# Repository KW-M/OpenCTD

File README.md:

# OpenCTD SSROV / Education Edition!

This fork contains a modified version of the [OpenCTD](https://github.com/OceanographyforEveryone/OpenCTD) designed to be more reliable, easy to use, and useful as a hands-on classroom teaching tool - Developed for the [SSROV Summer Camp](https://ssrovcamp.org/) - Funding provided by the camp and the National Science Foundation

**Improvements**

- Much more reliable magnetic switch - hold to power on/off - works while fully sealed!
- Data download, calibration & configuration over USB - removes the need to take anything out of the tube or change firmware for use & calibration.
- Supports realtime plotting of sensors via the Arduino serial plotter.
- Configurable sample rate for fast response or extended battery life.
- Bright status LEDs that work in sunlight
- Includes proto space for extending with your own sensors or components.
- Built in slots for ambient lux and 9-axis orientation sensors.
- Connectors make major conmponents, mainboard and tube easily replaceable.
- Factory assembly PCB design - less soldering required and better components for very resonable prices via JLCPCB (30$ + shipping for 5 assembled boards).

**There are many other great open source CTDs used for different applications**

CTDizzle: https://github.com/IanTBlack/CTDizzle

Arduino-based Sonde: https://github.com/glockridge/DrifterApplication

OpenCTD: https://github.com/OceanographyforEveryone/OpenCTD

PiCTD: https://github.com/haanhouse/pictd

## Make your own

> Build and ordering guides comming soon

All things related to the SSROV OpenCTD are found in the [SSROV CTD](./SSROV%20CTD/) folder including:

- [Source code](./SSROV%20CTD/Software/Firmware/ssrov_ctd_code) in Arduino c++ and [pre-compiled binaries](./SSROV%20CTD/Software/Firmware/ssrov_ctd_code/build) for the Adafruit Feather Adalogger - M0 microcontroller.
- [PCB designs](./SSROV%20CTD/Hardware/Electronics/PCB/ssrov-kicad-openctd) in KiCad and exported [pcb trace & assembly files](./SSROV%20CTD/Hardware/Electronics/PCB/ssrov-kicad-openctd/production/) for ordering assembled circuit boards from JLCPCB.
- [3D Printer files](./SSROV%20CTD/Hardware/3D-Prints) and [CAD Designs](https://cad.onshape.com/documents/1210ba157fe929ee8ac86200/w/c68b7dc340291ef5042e473d/e/f126e805a19383355f9e1651) for Onshape.

Submit a github issue and let us know if you want make one or modify for your usecase! - We are happy to help!

### Development Notes:

> Please be advised that the rubber o-rings in the yellow Cherne brand endcaps is much stiffer than the rubber used in other endcap brands and has been found to fail consistently in cold water. We do not recommend using Cherne endcaps in your CTD build.
>
> Some batteries ordered from Amazon have the positive and negative termninal reversed. Please check battery polarity before attempting to power your CTD.

# OpenCTD: Oceanography for Everyone

**BELOW IS THE README FROM THE ORIGNAL OPENCTD PROJECT**

- Directions here do not nessisarily apply to ssrov CTD.

The [OpenCTD Construction and
Operation](https://github.com/OceanographyforEveryone/OpenCTD/tree/main/Documentation/Manual)
manual provides a comprehensive, step-by-step guide to building your own
OpenCTD, with a standard construction pathway as well as numerous alternatives
depending on parts availability and technical skills.

The OpenCTD [core software](https://github.com/OceanographyforEveryone/OpenCTD/tree/main/Software) is designed
to be used with an M0-style Arduino microcontroller, for which we recommend the
[Adafruit Adalogger Feather M0](https://www.adafruit.com/product/2796).

---

There is something radical about making and using your own scientific
instruments. The structure of scientific inquiry has coalesced around a model
that is, in general, both expensive and exclusive. This centralizes knowledge
production within a small circle of individuals, organizations, and
institutions who have access to substantial financial resources. This circle
rarely reflects the breadth of identities, experiences, and ways of knowing
that are most directly connected to the places being explored.

By building your own instruments to study and understand the natural world, you
are expanding the circle of knowledge production. A scientist who can make
their own instruments is not beholden to the cycles of funding and access that
constrain formal, institutional inquiry. A researcher who can build and repair
their own equipment is not dependent on the whims of academic sentiment to
decide what is and is not worthy of study. A community leader who has the tools
to create their own data does not have to wait for institutions to take notice
of an emerging crisis before taking action.

.jpg>)

**You don’t need to ask for permission to understand your world.**

Nowhere is this inequality of access more pronounced than in the ocean
sciences, where all but a few entities have the capital to mount major
oceanographic research campaigns. Even localized coastal research can be
thwarted by lack of access to vessels, equipment, and instruments. As the need
to understand the dramatic changes at the surface and beneath the waves
accelerates, baring the participation of ocean stakeholders erodes our
power to understand, anticipate, and mitigate those changes.

The ocean belongs to everyone. The tools to study the ocean should be
accessible to anyone with the curiosity and motivation to pursue that inquiry.
Chief among these tools is the workhorse of oceanography, the CTD, an
instrument that measures salinity, temperature, and depth. By these
characteristics, scientists can begin to unlock ocean patterns hidden beneath
the sea's surface.

CTDs come in a variety of shapes, sizes, and applications. Most oceanographic
research vessels have a CTD connected to a rosette platform, which houses other
instruments and collects water samples in parallel with real-time data. CTDs
are also commonly attached to fixed moorings, autonomous underwater vehicles
(AUVs), remote-operated vehicles (ROVs), and even to marine animals.

Unfortunately, commercial CTDs are expensive. The most affordable models cost
several thousand dollars. For near-shore oceanographic research on the
relatively shallow continental shelf, this cost can be prohibitive. This
effectively excludes formal researchers from low and middle income countries,
and small island states. Even in high-income countries, formal researchers at
teaching institutions or at early career stages may also find themselves priced
out of ocean research. Informal researchers such as citizen oceanographers,
educators, conservation and management practitioners and students of all levels
face severe challenges accessing expensive scientific instruments.

### Build Your Own CTD

The OpenCTD is a low-cost, open-source CTD designed for budget-restricted
scientists, educators, and researchers working in nearshore coastal ecosystems.
In these waterways, entire research projects can be conducted for less than the
cost of a commercial CTD. OpenCTD was developed by a core team of marine
ecologists in collaboration with a community of scientists, engineers, makers,
and conservation practitioners from around the world. It is assembled from
components commonly available at large hardware stores or through major online
retailers. An Arduino-based microcontroller controls an array of sensors sealed
within a PVC pipe. Power is provided by a standard 3.7V lithium polymer battery
and data are stored in a tab-delimited text file accessed via SD card. All
OpenCTD software is released open source with no restrictions on use.

The OpenCTD is designed to be built by the end-user, providing both access to
the tools of oceanography as well as the skills to maintain, repair, and
replace OpenCTDs. For scientists working in remote settings, the repairability
of the OpenCTD is intended to prevent equipment failures from spiraling into
project failures. For educators seeking novel, in-depth, hands-on STEM
experience for advanced students, the process of building an OpenCTD offers an
introduction to coding, 3D-printing, hardware prototyping, and electronics.
Construction of an OpenCTD can provide a practical foundation for courses in
oceanography and marine or environmental science.

### Core Resources

The [OpenCTD Construction and
Operation](https://github.com/OceanographyforEveryone/OpenCTD/tree/main/Documentation/Manual)
manual provides a comprehensive, step-by-step guide to building your own
OpenCTD, with a standard construction pathway as well as numerous alternatives
depending on parts availability and technical skills. A shorter manual covering just the calibration process is also available.

The OpenCTD [core software](https://github.com/OceanographyforEveryone/OpenCTD/tree/main/Software) is designed
to be used with an M0-style Arduino microcontroller, for which we recommend the
[Adafruit Adalogger Feather M0](https://www.adafruit.com/product/2796).

You can find all the Arduino libraries as described in the manual, as well as
software for calibrating the conductivity sensors in
[Support](https://github.com/OceanographyforEveryone/OpenCTD/tree/main/Software/Support).

Hardware file for both 3D printable components and the control unit PBC can be found in [Hardware](https://github.com/OceanographyforEveryone/OpenCTD/tree/main/Hardware)

**Updated 8/27/2024**

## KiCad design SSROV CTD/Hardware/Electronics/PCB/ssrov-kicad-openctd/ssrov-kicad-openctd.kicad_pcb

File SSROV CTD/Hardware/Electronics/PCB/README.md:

# OpenCTD SSROV PCB

The OpenCTD main board is designed using [KiCad](https://www.kicad.org/) and made to be fabricated and assembled using JLCPCB.

prebuilt gerber and assembly files can be found in [./ssrov-kicad-openctd/production/](./ssrov-kicad-openctd/production/)
video guide on ordering will be shared soon

Factory Assembled main board:

Main board after manual assembly including optional components:

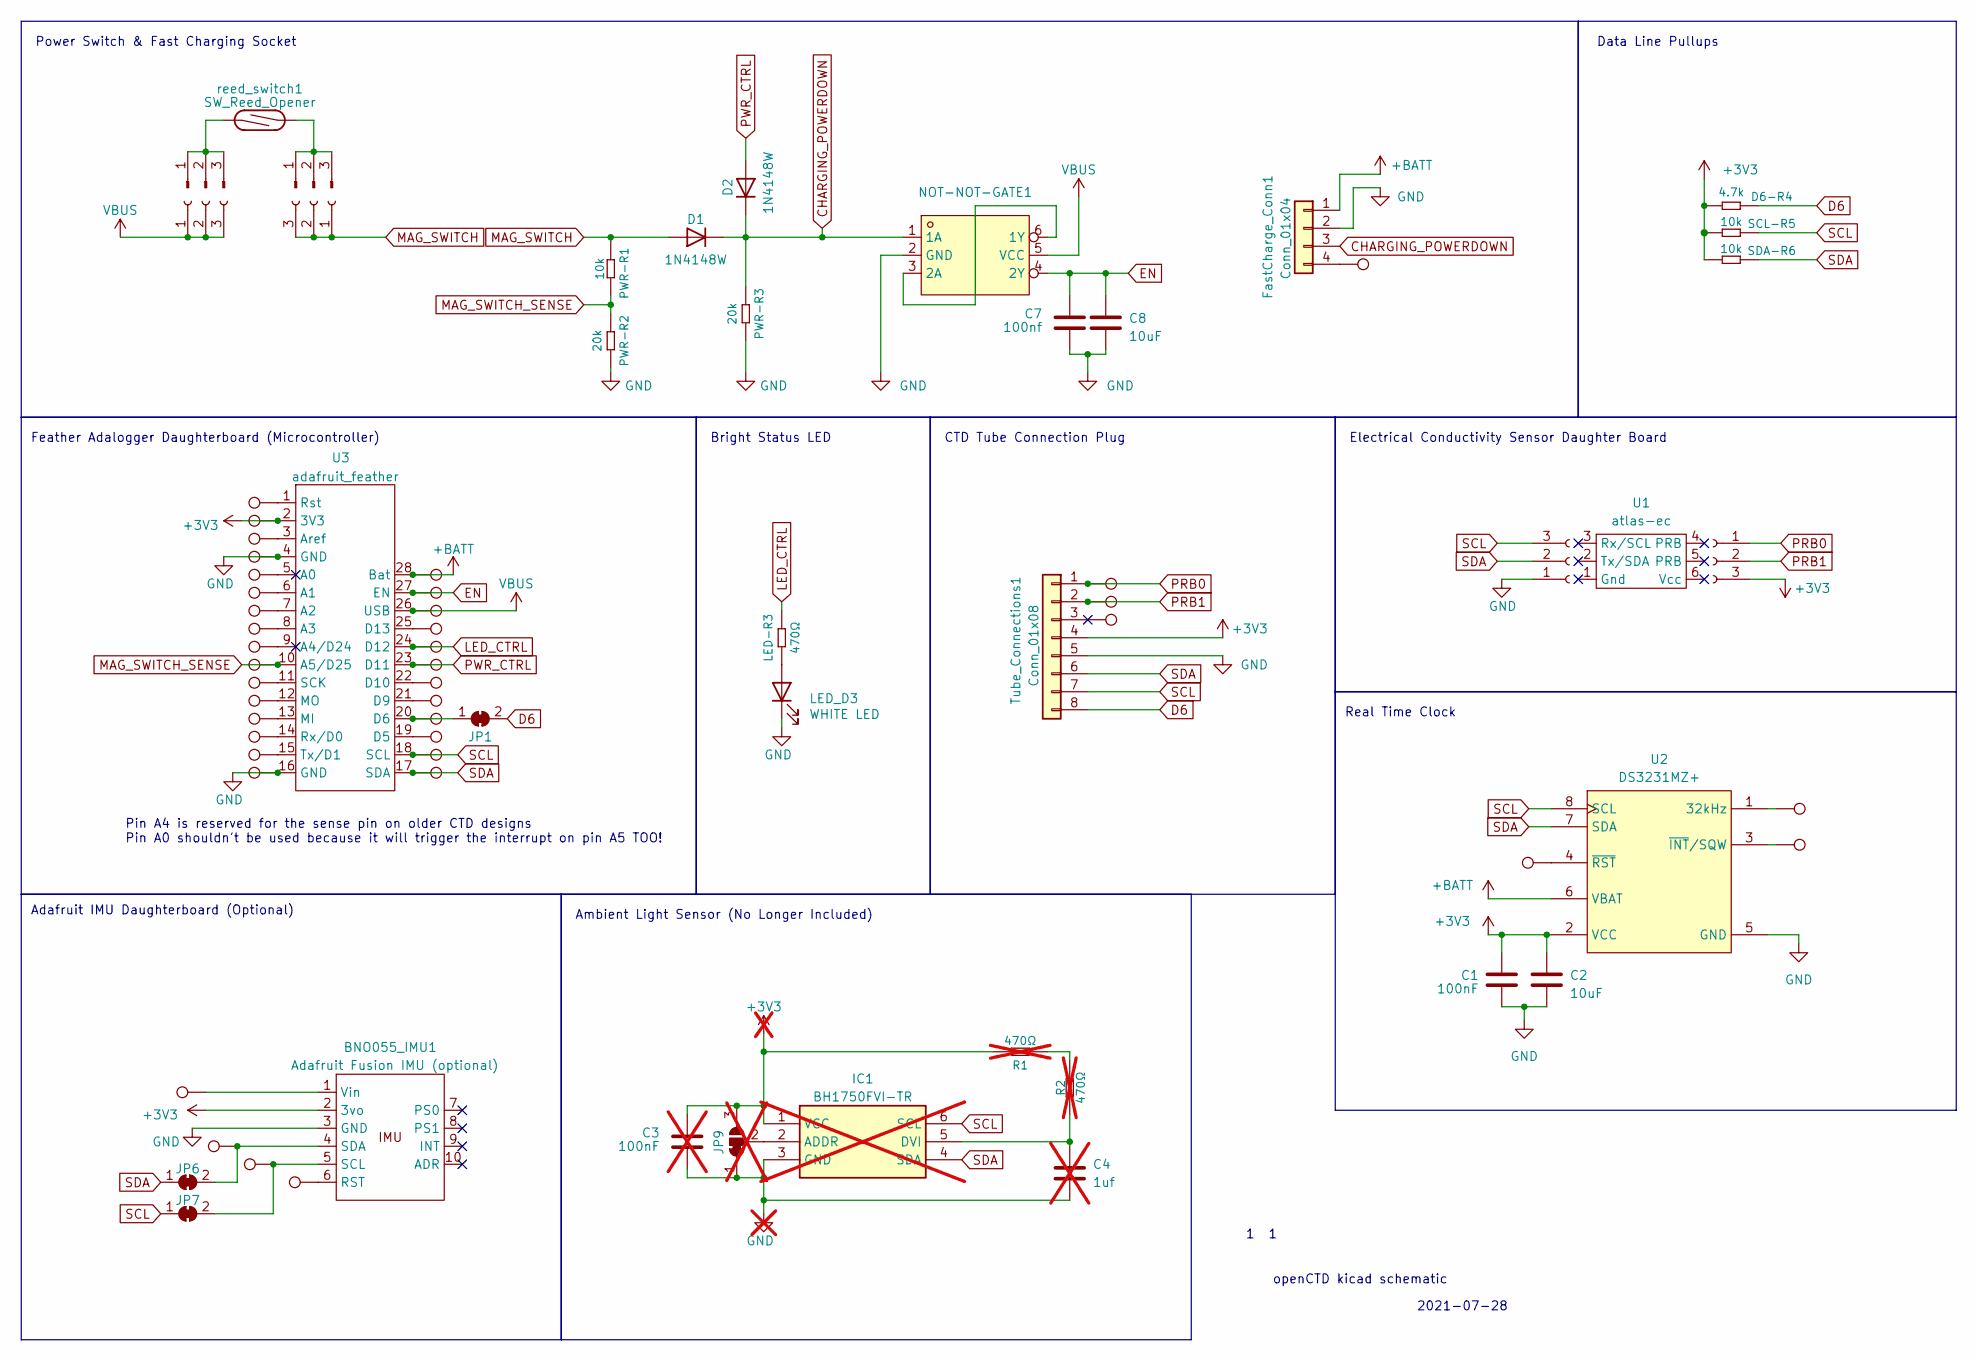
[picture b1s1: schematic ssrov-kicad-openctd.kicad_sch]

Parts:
BNO055_IMU1: Adafruit Fusion IMU (optional); Adafruit BNO055 IMU fusion breakout board
C1: 100nF; C_0402_1005Metric; LCSC Part C1525
C2, C8: 10uF; C_0402_1005Metric; LCSC Part C15525
C3: 100nF; C_0402_1005Metric; LCSC Part C1525; not fitted
C4: 1uf; C_0402_1005Metric; LCSC Part C52923; not fitted
C7: 100nf; C_0402_1005Metric; LCSC Part C1525
D1, D2: 1N4148W; D_SOD-123; LCSC Part C81598
D6-R4: 4.7k; R_0402_1005Metric; LCSC Part C25900
EC_Conn_A1: Conn_01x03_Female; HDR-SMD_3P-P2.54-V-M-LS4.8_R1; LCSC Part C42379196
EC_Conn_B5: Conn_01x03_Female; HDR-SMD_3P-P2.54-V-M-LS4.8_R1; LCSC Part C42379196
FastCharge_Conn1: Conn_01x04; Molex_KK_Female_Horizontal_PinHeader_1x04
IC1: BH1750FVI-TR; WSOF6; Mouser Part Number 755-BH1750FVI-TR; not fitted
J1, J3: Conn_01x03_Pin; PinHeader_1x03_P2.54mm_Vertical
JP1, JP6, JP7: SolderJumper_2_Bridged; Cuttable_SolderJumper-2_P1.3mm_Bridged_RoundedPad1.0x1.5mm
JP9: SolderJumper_3_Bridged12; SolderJumper-3_P1.3mm_Bridged12_RoundedPad1.0x1.5mm; not fitted
LED-R3: 470Ω; R_0402_1005Metric; LCSC Part C25117
LED_D3: WHITE LED; LED_0603_1608Metric; LCSC Part C2290
NOT-NOT-GATE1: SN74LVC2G14DBVR; SOT-23-6_L2.9-W1.6-P0.95-LS2.8-BL; LCSC Part C12401
PWR-R1: 10k; R_0402_1005Metric; LCSC Part C25744
PWR-R2, PWR-R3: 20k; R_0402_1005Metric; LCSC Part C25765
R1, R2: 470Ω; R_0402_1005Metric; LCSC Part C25117; not fitted
Reed_Switch_Conn1, Reed_Switch_Conn2: Conn_01x03_Female; HDR-SMD_3P-P2.54-V-M-LS4.8_R1; LCSC Part C42379196
SCL-R5: 10k; R_0402_1005Metric; LCSC Part C25744
SDA-R6: 10k; R_0402_1005Metric; LCSC Part C25744
TP1, TP2, TP3, TP4, TP5, TP6, TP7, TP8, TP9, TP10, TP11, TP12, TP13, TP14, TP15, TP21, TP22, TP23, TP24, TP25, TP26, TP27, TP28, TP29, TP30, TP31, TP32, TP33, TP34, TP35, TP36, TP37, TP38, TP39, TP40, TP42, TP43, TP44, TP46: test.point_single_pad_0.8
Tube_Connections1: Conn_01x08; SHDRRA8W62P0X254_1X8_2032X818X660P 22-05-3081
U1: atlas-ec; Atlas_EC_Silkscreen_Only
U2: DS3231MZ+; SOIC-8_L4.9-W3.9-P1.27-LS6.0-BL; LCSC Part C107410
U3: adafruit_feather; Adafruit_Feather_With2MountingHoles
reed_switch1: SW_Reed_Opener; Littelfuse Reed Switch 59050-1-S

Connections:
+3V3: BNO055_IMU1.2 (3vo), C1.2, C2.1, C3.2, D6-R4.1, EC_Conn_B5.3, IC1.1 (VCC), JP9.3 (B), R1.1, SCL-R5.1, SDA-R6.1, TP22.1, Tube_Connections1.4, U2.2 (VCC), U3.2 (3V3); also elsewhere on the board
+BATT: FastCharge_Conn1.1, TP1.1, U2.6 (VBAT), U3.28 (Bat)
CHARGING_POWERDOWN: D1.1 (K), D2.1 (K), FastCharge_Conn1.3, NOT-NOT-GATE1.1 (1A), PWR-R3.2
D6: D6-R4.2, JP1.2 (B), Tube_Connections1.8
EN: C7.2, C8.1, NOT-NOT-GATE1.4 (2Y), TP2.1, U3.27 (EN)
GND: BNO055_IMU1.3 (GND), C1.1, C2.2, C3.1, C4.2, C7.1, C8.2, EC_Conn_A1.1, FastCharge_Conn1.2, IC1.3 (GND), JP9.1 (A), LED_D3.1 (K), NOT-NOT-GATE1.2 (GND), PWR-R2.1, PWR-R3.1, TP24.1, TP36.1, Tube_Connections1.5, U2.5 (GND), U3.4 (GND), U3.16 (GND); also elsewhere on the board
LED_CTRL: LED-R3.1, TP5.1, U3.24 (D12)
MAG_SWITCH: D1.2 (A), PWR-R1.2, Reed_Switch_Conn2.1, Reed_Switch_Conn2.2, Reed_Switch_Conn2.3
MAG_SWITCH_SENSE: PWR-R1.1, PWR-R2.2, TP30.1, U3.10 (A5/D25)
unnamed: BNO055_IMU1.6 (RST), TP42.1
unnamed: BNO055_IMU1.5 (SCL), JP7.2 (B), TP43.1
unnamed: BNO055_IMU1.4 (SDA), JP6.2 (B), TP44.1
unnamed: BNO055_IMU1.1 (Vin), TP40.1
unnamed: C4.1, IC1.5 (DVI), R2.2
unnamed: FastCharge_Conn1.4, TP46.1
unnamed: IC1.2 (ADDR), JP9.2 (C)
unnamed: J1.1, J1.2, J1.3, reed_switch1.2
unnamed: J3.1, J3.2, J3.3, reed_switch1.1
unnamed: JP1.1 (A), TP9.1, U3.20 (D6)
unnamed: LED-R3.2, LED_D3.2 (A)
unnamed: NOT-NOT-GATE1.3 (2A), NOT-NOT-GATE1.6 (1Y)
unnamed: R1.2, R2.1
unnamed: TP39.1, U2.1 (32kHz)
unnamed: TP38.1, U2.3 (~INT/SQW)
unnamed: TP37.1, U2.4 (~RST)
unnamed: TP25.1, U3.5 (A0)
unnamed: TP26.1, U3.6 (A1)
unnamed 45: TP27.1, U3.7 (A2); also elsewhere on the board
unnamed: TP28.1, U3.8 (A3)
unnamed: TP29.1, U3.9 (A4/D24)
unnamed: TP23.1, U3.3 (Aref)
unnamed: TP10.1, U3.19 (D5)
unnamed: TP8.1, U3.21 (D9)
unnamed: TP7.1, U3.22 (D10)
unnamed: TP4.1, U3.25 (D13)
unnamed: TP33.1, U3.13 (MI)
unnamed: TP32.1, U3.12 (MO)
unnamed: TP21.1, U3.1 (Rst)
unnamed 56: TP34.1, U3.14 (Rx/D0); also elsewhere on the board
unnamed: TP31.1, U3.11 (SCK)
unnamed 58: TP35.1, U3.15 (Tx/D1); also elsewhere on the board
PRB0: EC_Conn_B5.1, TP15.1, Tube_Connections1.1
PRB1: EC_Conn_B5.2, TP14.1, Tube_Connections1.2
PWR_CTRL: D2.2 (A), TP6.1, U3.23 (D11)
SCL: EC_Conn_A1.3, IC1.6 (SCL), JP7.1 (A), SCL-R5.2, TP11.1, Tube_Connections1.7, U2.8 (SCL), U3.18 (SCL); also elsewhere on the board
SDA: EC_Conn_A1.2, IC1.4 (SDA), JP6.1 (A), SDA-R6.2, TP12.1, Tube_Connections1.6, U2.7 (SDA), U3.17 (SDA); also elsewhere on the board
VBUS: NOT-NOT-GATE1.5 (VCC), Reed_Switch_Conn1.1, Reed_Switch_Conn1.2, Reed_Switch_Conn1.3, TP3.1, U3.26 (USB); also elsewhere on the board

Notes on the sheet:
Data Line Pullups
Electrical Conductivity Sensor Daughter Board
Bright Status LED
2021-07-28
Real Time Clock
Ambient Light Sensor (No Longer Included)
openCTD kicad schematic
Adafruit IMU Daughterboard (Optional)
Power Switch & Fast Charging Socket
Pin A4 is reserved for the sense pin on older CTD designs Pin A0 shouldn't be used because it will trigger the interrupt on pin A5 TOO!
CTD Tube Connection Plug
Feather Adalogger Daughterboard (Microcontroller)

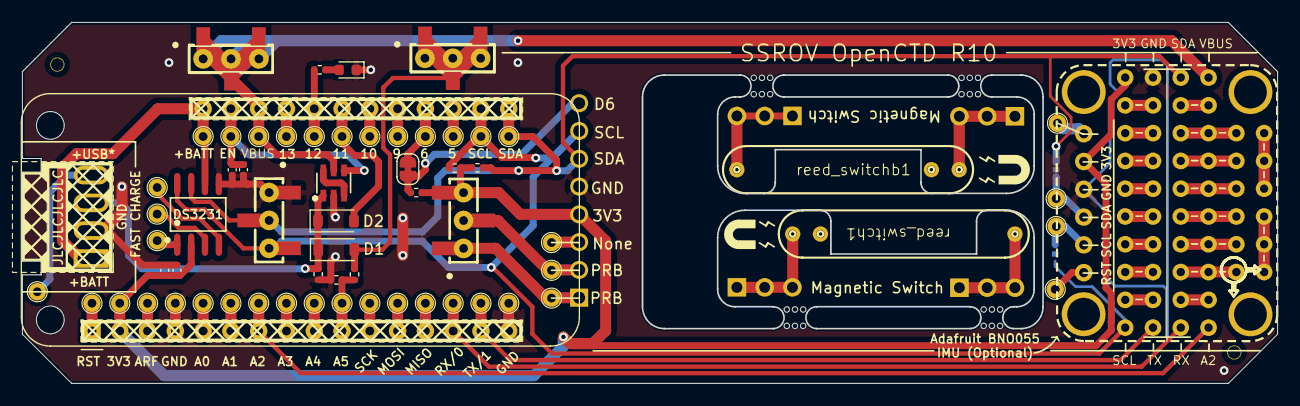
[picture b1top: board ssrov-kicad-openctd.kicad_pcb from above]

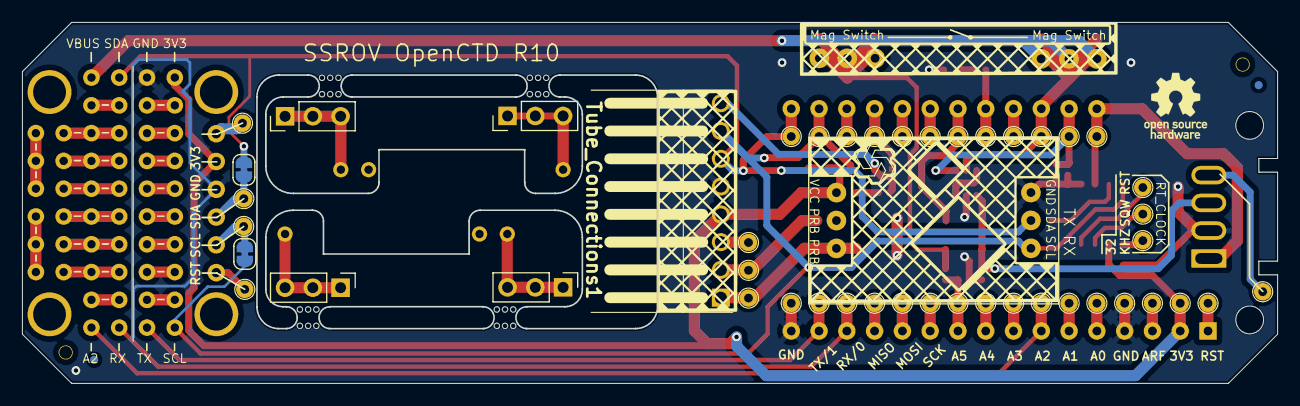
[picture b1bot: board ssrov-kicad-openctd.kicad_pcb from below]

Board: 2 copper layers, 114.7 x 33.0 mm, 81 parts (9 on the bottom side), 46 nets.

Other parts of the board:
JB1, JB3: Conn_01x03_Pin; PinHeader_1x03_P2.54mm_Vertical
OSHW_Logo: OSHW-Logo_5.7x6mm_SilkScreen
Perma_Breadboard_Area1: PermaProto_Breadboard_Area
mouse-bite-2mm-slot, mouse-bite-2mm-slot#2, mouse-bite-2mm-slot#3, mouse-bite-2mm-slot#4: VAL**; mouse-bite-2mm-slot
reed_switchb1: SW_Reed_Opener; Littelfuse Reed Switch 59050-1-S
top_hole1, top_hole1#2: JLCPCBA_mount_hole

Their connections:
+3V3: Perma_Breadboard_Area1.2; also elsewhere on the board
GND: Perma_Breadboard_Area1.3; also elsewhere on the board
unnamed 45: Perma_Breadboard_Area1.38; also elsewhere on the board
unnamed 56: Perma_Breadboard_Area1.37; also elsewhere on the board
unnamed 58: Perma_Breadboard_Area1.36; also elsewhere on the board
Reed_switch_b1: JB1.1, JB1.2, JB1.3, reed_switchb1.2
Reed_switch_b3: JB3.1, JB3.2, JB3.3, reed_switchb1.1
SCL: Perma_Breadboard_Area1.34; also elsewhere on the board
SDA: Perma_Breadboard_Area1.36; also elsewhere on the board
VBUS: Perma_Breadboard_Area1.39; also elsewhere on the board

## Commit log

2023-08-08 Add SSROV CTD Hardware
2023-08-12 Add SSROV CTD Software
2024-02-08 fix footprint component libs location
2024-09-09 updated software sept 2024
2024-09-09 updated pcb design sept 2024
2024-09-09 Update Readme to talk about SSROV CTD
2024-09-09 Readme updates
2024-09-09 update 3d printing models and guide
2024-09-09 typo
2024-09-09 organization of ssrov-kicad and documentation updates
2024-09-27 Add tube build guide and organize hardware folder
2025-06-04 remove unused code examples from included libraries
2025-06-04 fix rare hang caused by interupt and i2c + removed interupt timer code
2025-06-04 OpenCTD SSROV PCB Board revision 10
2025-06-04 clean up kicad pcb file leftovers and readme
